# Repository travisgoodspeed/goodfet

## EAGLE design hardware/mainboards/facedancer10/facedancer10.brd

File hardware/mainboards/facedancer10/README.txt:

Facedancer10, a GoodFET for exploiting USB.
by Travis Goodspeed and Sergey Bratus
http://goodfet.sf.net/

The Facedancer board exposes a MAX3420 USB device controller to
Python, allowing a good neighbor to explore the vulnerabilities of
poorly written USB device drivers, prototype USB devices, or otherwise
play with USB as a network instead of as a magic school bus.

The MAX3420E part in active.lbr came from a tutorial by Andrew Greensted.
http://www.labbookpages.co.uk/circuits/max3420.html

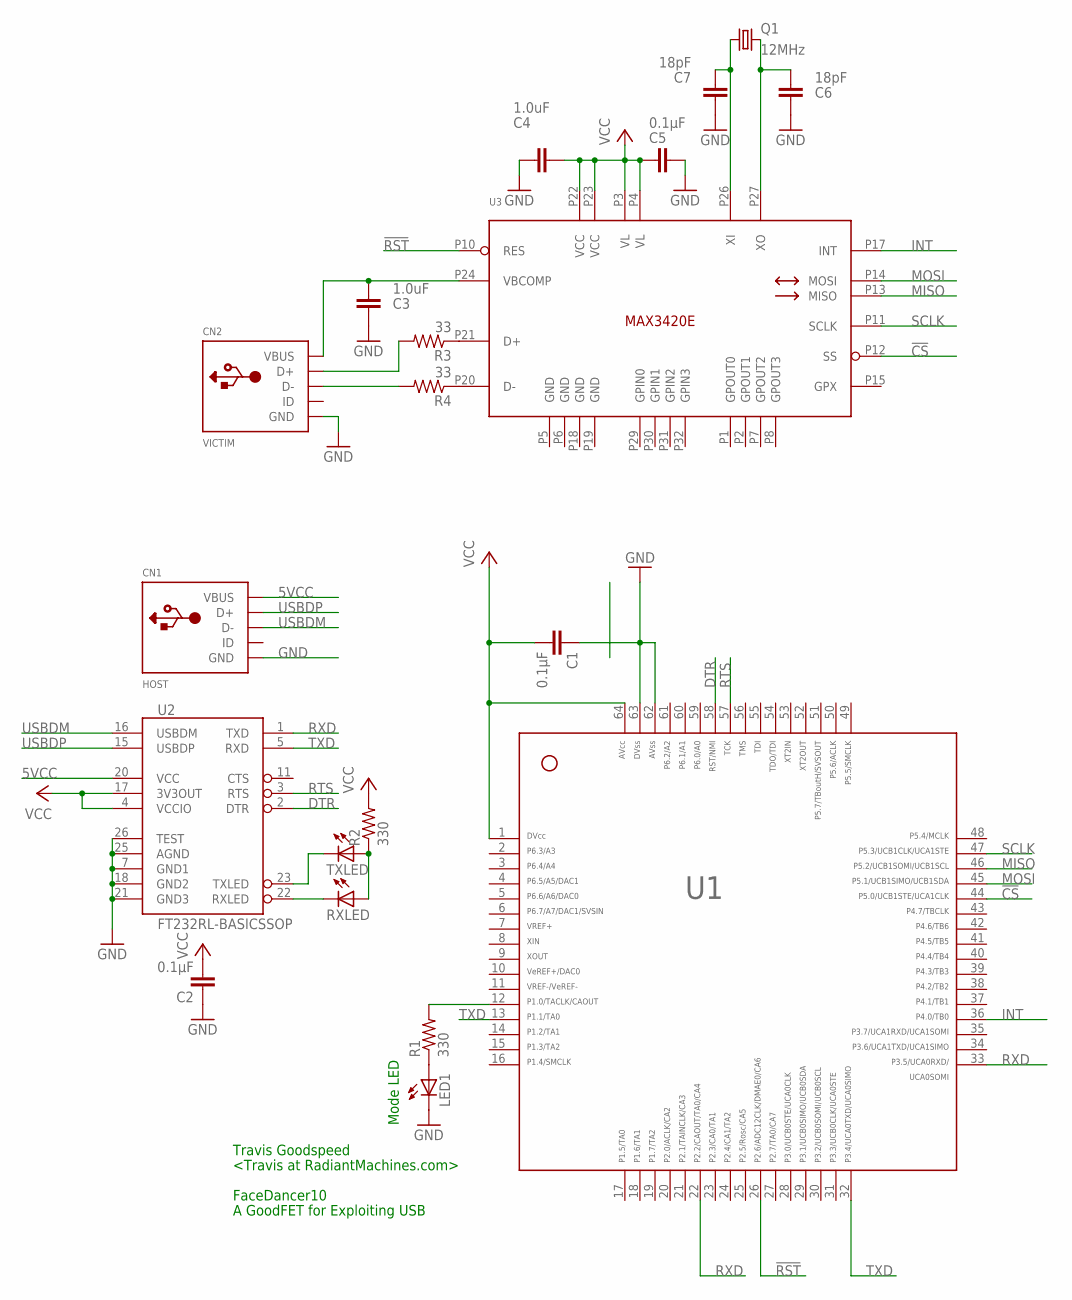
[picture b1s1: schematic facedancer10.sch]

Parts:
C1, C2, C5: 0.1µF; C0603
C3, C4: 1.0uF; C0603
C6, C7: 18pF; C0603
CN1: HOST; USB-MINIB
CN2: VICTIM; USB-MINIB
LED1: LEDCHIP-LED0603; CHIP-LED0603
Q1: 12MHz; HC49UP
R1, R2: 330; R0603
R3, R4: 33; R0603
RXLED: LEDCHIP-LED0603; CHIP-LED0603
TXLED: LEDCHIP-LED0603; CHIP-LED0603
U1: F261X---PM64; PM/PAG64
U2: FT232RL-BASICSSOP; SSOP28DB
U3: MAX3420ELQFP32; LQFP32

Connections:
5VCC: CN1.VBUS, U2.20 (VCC)
!CS: U1.44, U3.P12 (SS)
!RST: U1.26, U3.P10 (RES)
DTR: U1.58, U2.2 (DTR)
GND: C1.1, C2.1, C3.1, C4.1, C5.1, C6.1, C7.1, CN1.GND, CN2.GND, LED1.C, U1.62, U1.63, U2.7 (GND1), U2.18 (GND2), U2.21 (GND3), U2.25 (AGND), U2.26 (TEST), U3.P5 (GND), U3.P6 (GND), U3.P18 (GND), U3.P19 (GND)
INT: U1.36, U3.P17 (INT)
MISO: U1.46, U3.P13 (MISO)
MOSI: U1.45, U3.P14 (MOSI)
unnamed: R1.2, U1.12
unnamed: LED1.A, R1.1
unnamed: C7.2, Q1.1, U3.P26 (XI)
unnamed: C6.2, Q1.2, U3.P27 (XO)
unnamed: R3.1, U3.P21 (D+)
unnamed: RXLED.C, U2.22 (RXLED)
unnamed: TXLED.C, U2.23 (TXLED)
unnamed: R2.1, RXLED.A, TXLED.A
unnamed: R4.1, U3.P20 (D-)
unnamed: CN2.D-, R4.2
unnamed: CN2.D+, R3.2
RTS: U1.57, U2.3 (RTS)
RXD: U1.22, U1.33, U2.1 (TXD)
SCLK: U1.47, U3.P11 (SCLK)
TXD: U1.13, U1.32, U2.5 (RXD)
USBDM: CN1.D-, U2.16 (USBDM)
USBDP: CN1.D+, U2.15 (USBDP)
VBCOMP: C3.2, CN2.VBUS, U3.P24 (VBCOMP)
VCC: C1.2, C2.2, C4.2, C5.2, R2.2, U1.1, U1.64, U2.4 (VCCIO), U2.17 (3V3OUT), U3.P3 (VL), U3.P4 (VL), U3.P22 (VCC), U3.P23 (VCC)

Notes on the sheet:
Mode LED
Travis Goodspeed
<Travis at RadiantMachines.com>
FaceDancer10
A GoodFET for Exploiting USB

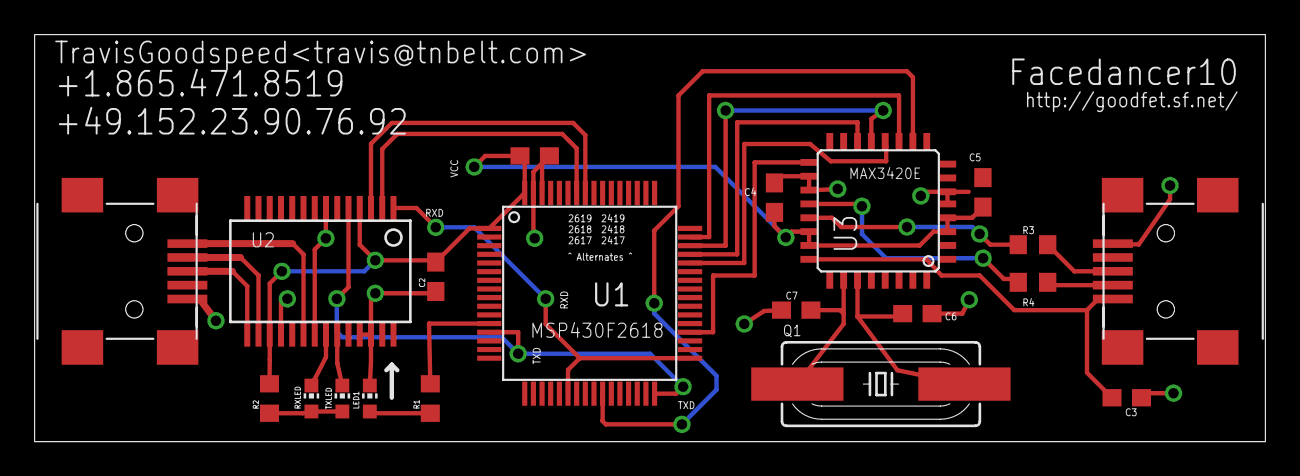
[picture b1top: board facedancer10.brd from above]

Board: 2 copper layers, 71.1 x 23.5 mm, 20 parts (0 on the bottom side), 27 nets.
